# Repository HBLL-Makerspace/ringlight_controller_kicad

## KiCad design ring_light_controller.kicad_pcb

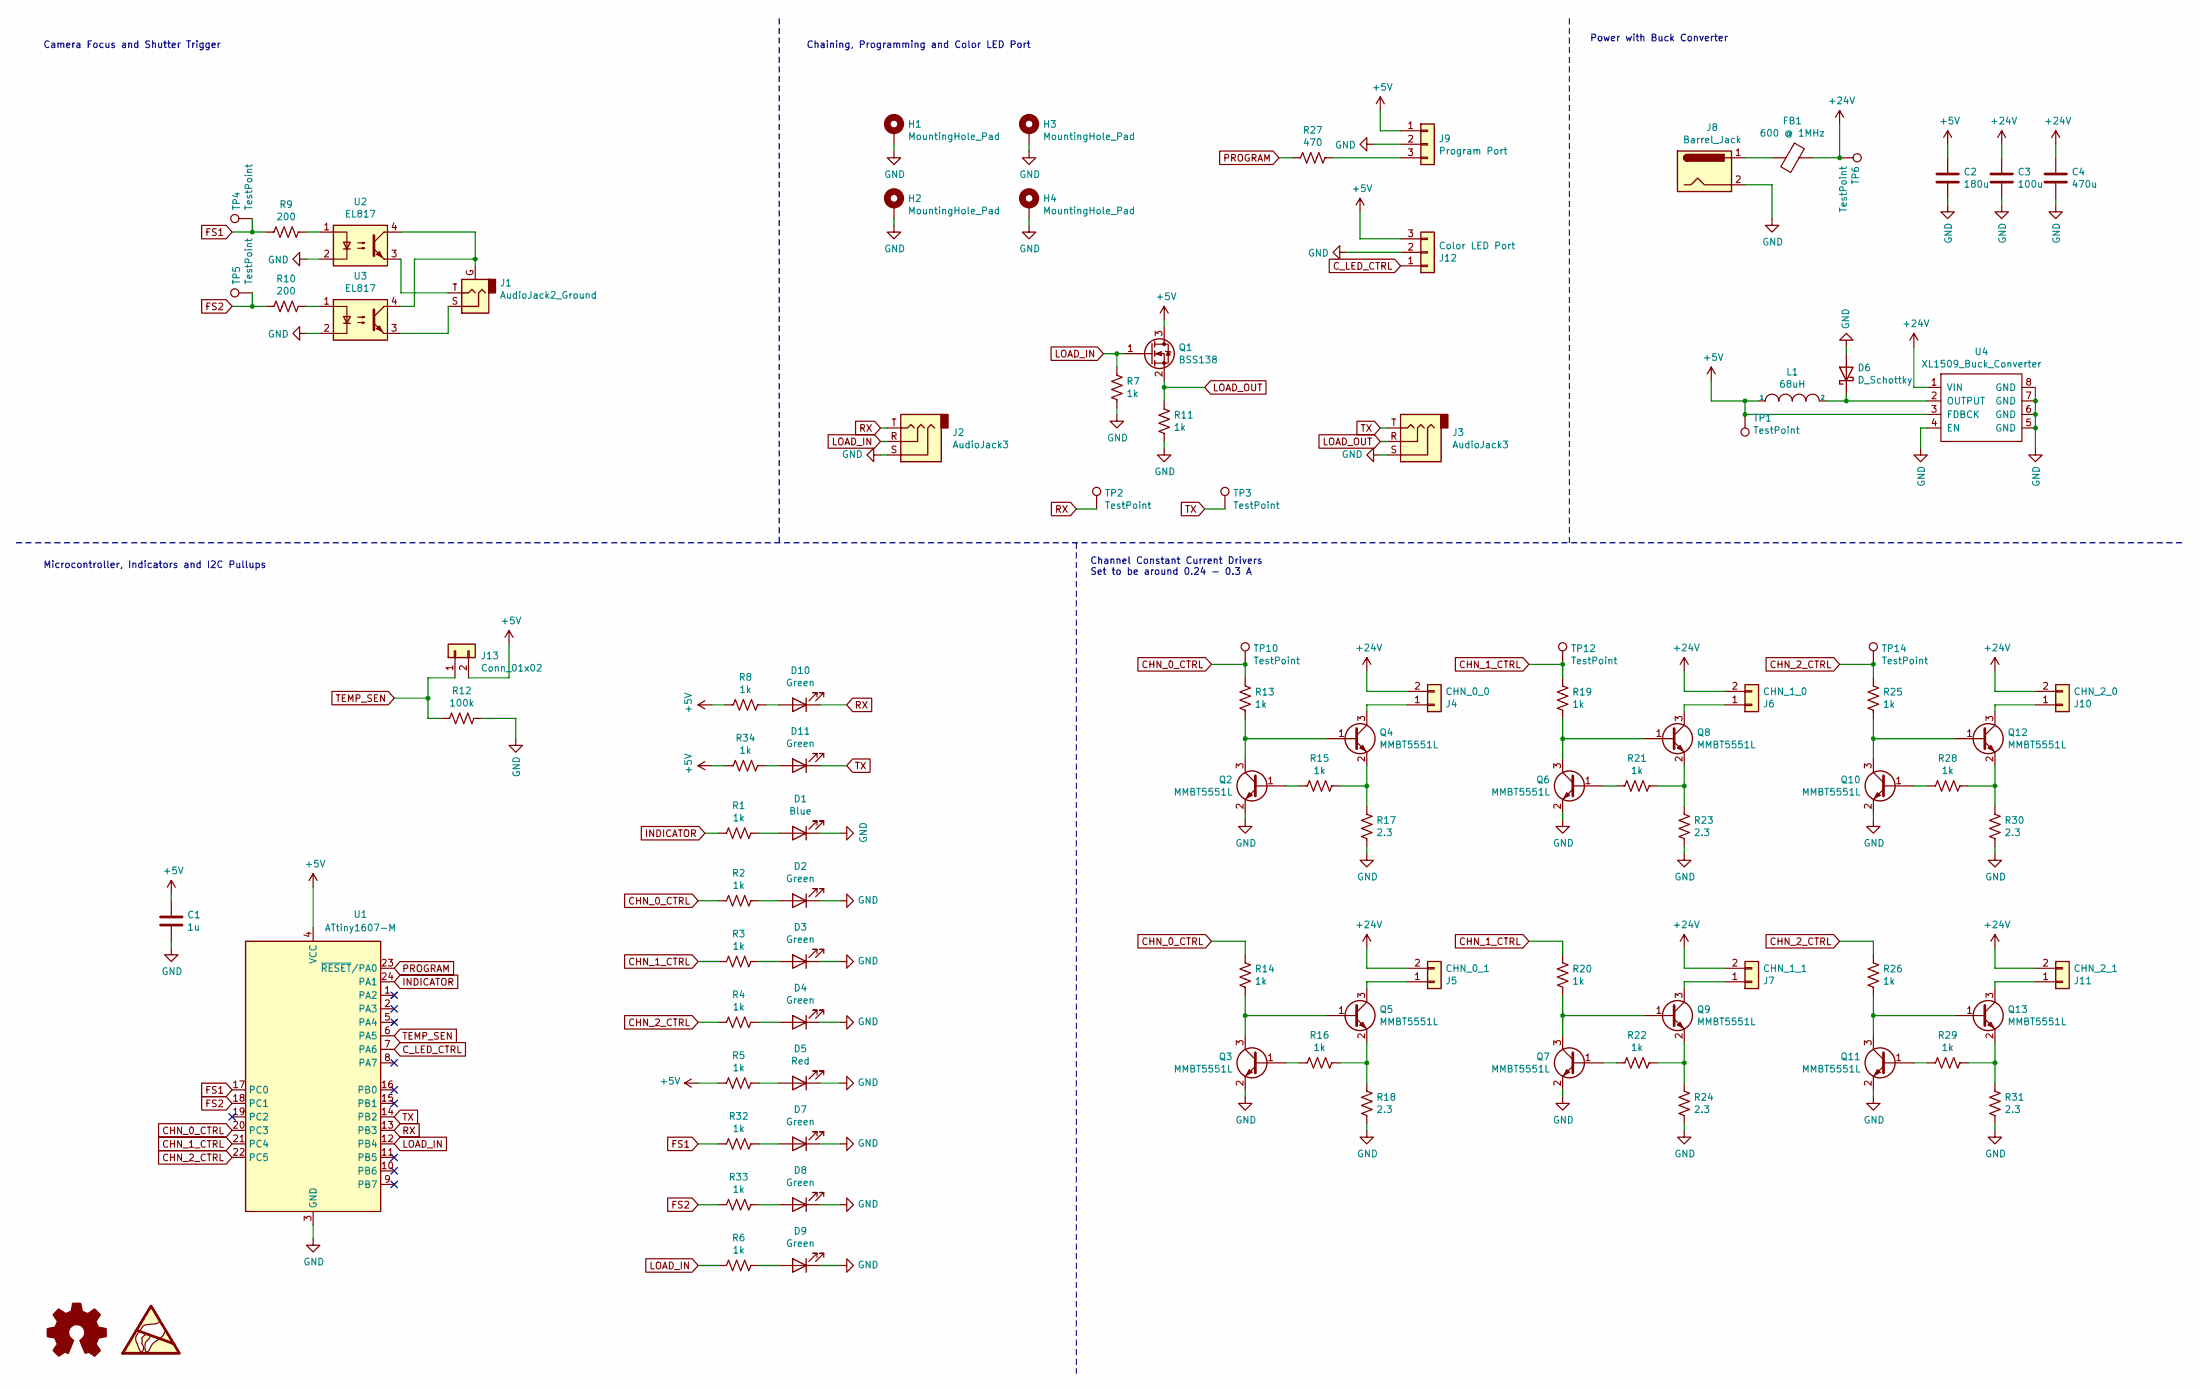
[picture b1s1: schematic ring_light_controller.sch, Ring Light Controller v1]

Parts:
C1: 1u; C_1206_3216Metric; LCSC Part # C1848
C2: 180u; C_Elec_10x10.2; LCSC Part # C487098
C3: 100u; C_Elec_6.3x5.4; LCSC Part # C134723
C4: 470u; C_Elec_10x10.2; LCSC Part # C249931
D1: Blue; LED_0603_1608Metric; LCSC Part # C72041
D2, D3, D4, D7, D8, D9, D10, D11: Green; LED_0603_1608Metric; LCSC Part # C72043
D5: Red; LED_0603_1608Metric; LCSC Part # C2286
D6: D_Schottky; D_SOD-123; LCSC Part # C8598
FB1: 600 @ 1MHz; L_0805_2012Metric; LCSC Part # C1017
H1, H2, H3, H4: MountingHole_Pad; MountingHole_5.3mm_M5_Pad_Via
J1: AudioJack2_Ground; Jack_2.5mm_PJ-2342-SMT; LCSC Part # C397356
J2, J3: AudioJack3; Jack_3.5mm_BOOMELE_C18594-SMT_Horizontal; LCSC C18594
J4: CHN_0_0; JST_XH_B2B-XH-AM_1x02_P2.50mm_Vertical
J5: CHN_0_1; JST_XH_B2B-XH-AM_1x02_P2.50mm_Vertical
J6: CHN_1_0; JST_XH_B2B-XH-AM_1x02_P2.50mm_Vertical
J7: CHN_1_1; JST_XH_B2B-XH-AM_1x02_P2.50mm_Vertical
J8: Barrel_Jack; BarrelJack_Horizontal
J9: Program Port; PinHeader_1x03_P2.54mm_Vertical
J10: CHN_2_0; JST_XH_B2B-XH-AM_1x02_P2.50mm_Vertical
J11: CHN_2_1; JST_XH_B2B-XH-AM_1x02_P2.50mm_Vertical
J12: Color LED Port; JST_XH_B3B-XH-AM_1x03_P2.50mm_Vertical
J13: Conn_01x02; JST_XH_B2B-XH-AM_1x02_P2.50mm_Vertical
L1: 68uH; L_SUNLORD_SWRB1205S_12.5x12.5mm_H6mm; LCSC Part # C169388
Q1: BSS138; SOT-23; LCSC Part # C2145
Q2, Q3, Q4, Q5, Q6, Q7, Q8, Q9, Q10, Q11, Q12, Q13: MMBT5551L; SOT-23; LCSC Part # C2145
R1, R2, R3, R4, R5, R6, R32, R33: 1k; R_0603_1608Metric; LCSC Part # C21190
R7, R11, R13, R14, R15, R16, R19, R20, R21, R22, R25, R26, R28, R29: 1k; R_0402_1005Metric; LCSC Part # C11702
R8, R34: 1k; R_0402_1005Metric; LCSC Part # C21190
R9, R10: 200; R_0402_1005Metric; LCSC Part # C11702
R12: 100k; R_0402_1005Metric; LCSC Part # C25741
R17, R18, R23, R24, R30, R31: 2.3; R_1206_3216Metric; LCSC Part # C247504
R27: 470; R_0402_1005Metric; LCSC Part # C25117
TP1, TP2, TP3, TP4, TP5, TP6, TP10, TP12, TP14: TestPoint; TestPoint_Pad_D1.0mm
U1: ATtiny1607-M; QFN-24-1EP_4x4mm_P0.5mm_EP2.6x2.6mm
U2, U3: EL817; SOIC254P1030X390-4N; LCSC Part # C106900
U4: XL1509_Buck_Converter; SOP-8_3.9x4.9mm_P1.27mm; LCSC Part # C61063

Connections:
+5V: C1.1, C2.1, J9.1, J12.3, J13.2, L1.1, Q1.3 (D), R5.2, R8.2, R34.2, TP1.1, U1.4 (VCC), U4.3 (FDBCK)
+24V: C3.1, C4.1, FB1.1, J4.2, J5.2, J6.2, J7.2, J10.2, J11.2, TP6.1, U4.1 (VIN)
CHN_0_CTRL: R2.2, R13.1, R14.1, TP10.1, U1.20 (PC3); also elsewhere on the board
CHN_1_CTRL: R3.2, R19.1, R20.1, TP12.1, U1.21 (PC4); also elsewhere on the board
CHN_2_CTRL: R4.2, R25.1, R26.1, TP14.1, U1.22 (PC5); also elsewhere on the board
C_LED_CTRL: J12.1, U1.7 (PA6)
FS1: R9.2, R32.2, TP4.1, U1.17 (PC0)
FS2: R10.2, R33.2, TP5.1, U1.18 (PC1)
GND: C1.2, C2.2, C3.2, C4.2, D1.1 (K), D2.1 (K), D3.1 (K), D4.1 (K), D5.1 (K), D6.2 (A), D7.1 (K), D8.1 (K), D9.1 (K), H1.1, H2.1, H3.1, H4.1, J2.S, J3.S, J8.2, J9.2, J12.2, Q2.2 (E), Q3.2 (E), Q6.2 (E), Q7.2 (E), Q10.2 (E), Q11.2 (E), R7.1, R11.1, R12.1, R17.2, R18.2, R23.2, R24.2, R30.2, R31.2, U1.3 (GND), U1.25 (GND), U2.2, U3.2, U4.4 (EN), U4.5 (GND), U4.6 (GND), U4.7 (GND), U4.8 (GND); also elsewhere on the board
INDICATOR: R1.2, U1.24 (PA1)
LOAD_IN: J2.R, Q1.1 (G), R6.2, R7.2, U1.12 (PB4)
LOAD_OUT: J3.R, Q1.2 (S), R11.2
unnamed: D1.2 (A), R1.1
unnamed: D2.2 (A), R2.1
unnamed: D3.2 (A), R3.1
unnamed: D4.2 (A), R4.1
unnamed: D5.2 (A), R5.1
unnamed: D6.1 (K), L1.2, U4.2 (OUTPUT)
unnamed: D7.2 (A), R32.1
unnamed: D8.2 (A), R33.1
unnamed: D9.2 (A), R6.1
unnamed: D10.2 (A), R8.1
unnamed: D11.2 (A), R34.1
unnamed: FB1.2, J8.1
unnamed: J1.G, U2.4, U3.4
unnamed: J1.S, U3.3
unnamed: J1.T, U2.3
unnamed: J4.1, Q4.3 (C)
unnamed: J5.1, Q5.3 (C)
unnamed: J6.1, Q8.3 (C)
unnamed: J7.1, Q9.3 (C)
unnamed: J9.3, R27.1
unnamed: J10.1, Q12.3 (C)
unnamed: J11.1, Q13.3 (C)
unnamed: Q2.1 (B), R15.2
unnamed: Q2.3 (C), Q4.1 (B), R13.2
unnamed: Q3.1 (B), R16.2
unnamed: Q3.3 (C), Q5.1 (B), R14.2
unnamed: Q4.2 (E), R15.1, R17.1
unnamed: Q5.2 (E), R16.1, R18.1
unnamed: Q6.1 (B), R21.2
unnamed: Q6.3 (C), Q8.1 (B), R19.2
unnamed: Q7.1 (B), R22.2
unnamed: Q7.3 (C), Q9.1 (B), R20.2
unnamed: Q8.2 (E), R21.1, R23.1
unnamed: Q9.2 (E), R22.1, R24.1
unnamed: Q10.1 (B), R28.2
unnamed: Q10.3 (C), Q12.1 (B), R25.2
unnamed: Q11.1 (B), R29.2
unnamed: Q11.3 (C), Q13.1 (B), R26.2
unnamed: Q12.2 (E), R28.1, R30.1
unnamed: Q13.2 (E), R29.1, R31.1
unnamed: R9.1, U2.1
unnamed: R10.1, U3.1
PROGRAM: R27.2, U1.23 (~RESET~/PA0)
RX: D10.1 (K), J2.T, TP2.1, U1.13 (PB3)
TEMP_SEN: J13.1, R12.2, U1.6 (PA5)
TX: D11.1 (K), J3.T, TP3.1, U1.14 (PB2)

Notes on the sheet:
Channel Constant Current Drivers Set to be around 0.24 - 0.3 A
Power with Buck Converter
Chaining, Programming and Color LED Port
Microcontroller, Indicators and I2C Pullups
Camera Focus and Shutter Trigger

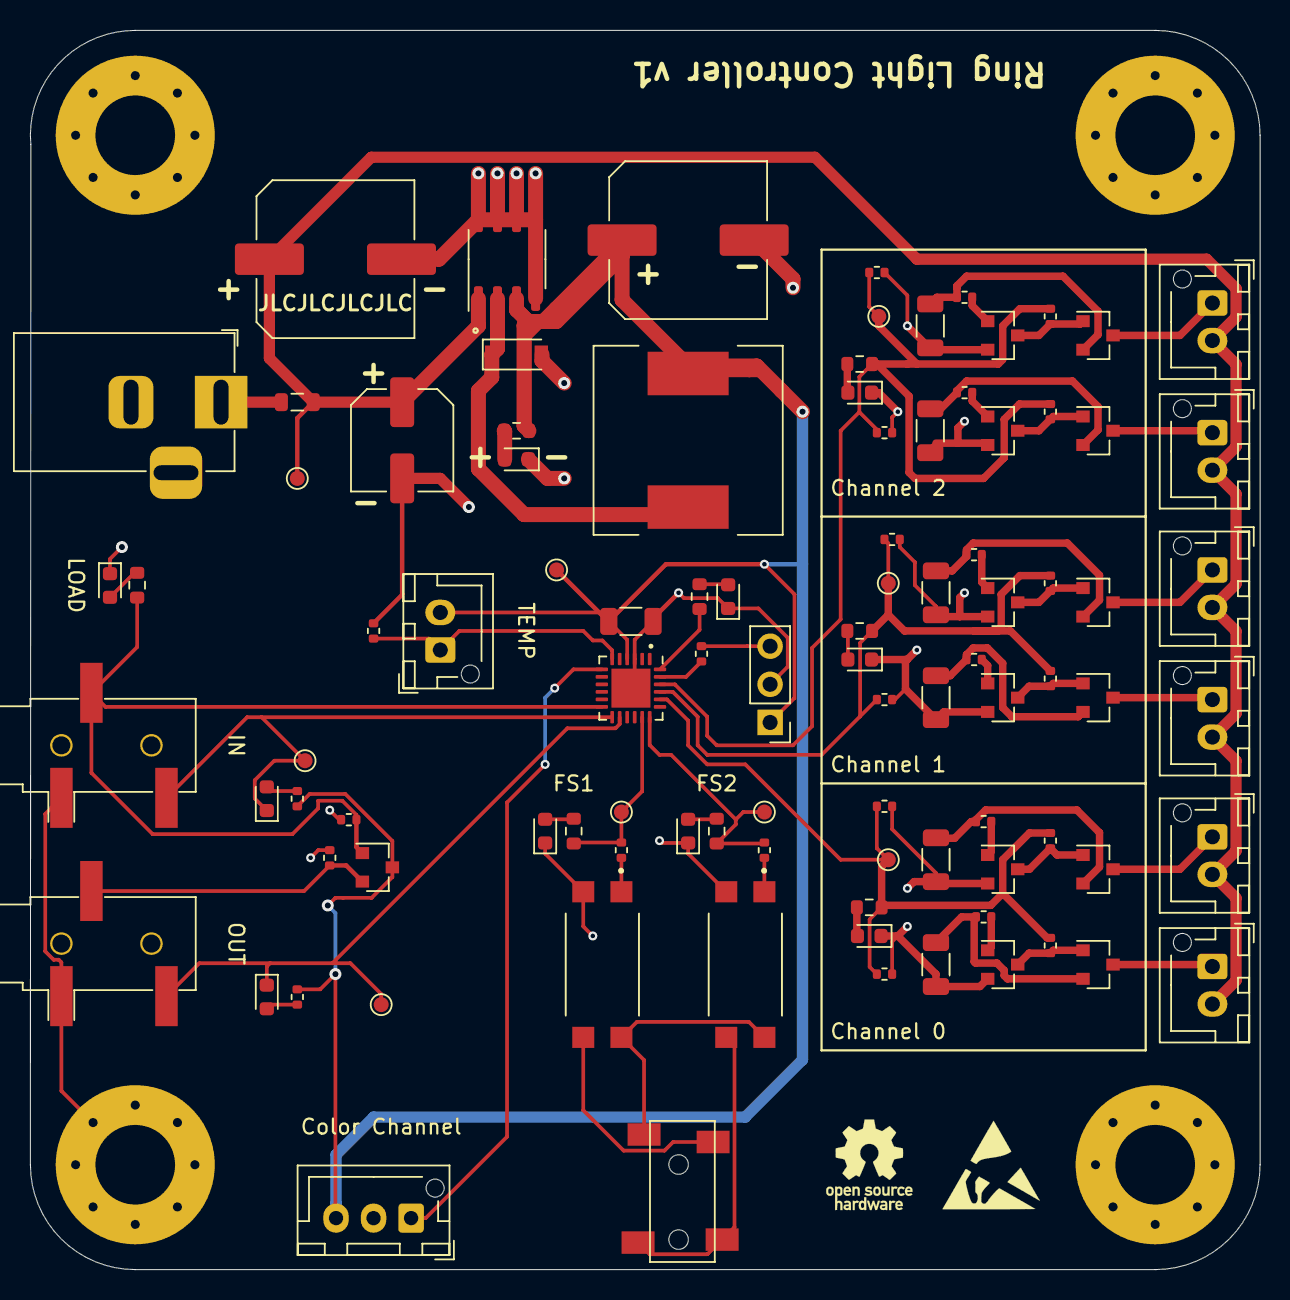
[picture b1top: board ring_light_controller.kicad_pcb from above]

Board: 2 copper layers, 81.9 x 82.6 mm, 100 parts (0 on the bottom side), 58 nets.

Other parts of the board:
R35, R36, R37, R38, R39, R40: 1k; R_0402_1005Metric

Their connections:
CHN_0_CTRL: R35.2, R36.2; also elsewhere on the board
CHN_1_CTRL: R37.2, R38.2; also elsewhere on the board
CHN_2_CTRL: R39.2, R40.2; also elsewhere on the board
GND: R35.1, R36.1, R37.1, R38.1, R39.1, R40.1; also elsewhere on the board

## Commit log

2021-07-09 Updated footprints to work with JLCPCB assembly parts
2021-07-20 updated pcb
2021-07-20 updated version numbering
2021-07-27 updated connecters to 3.5mm, and made opto resistors smaller in value
2021-07-29 slight changes
2021-07-30 fixed opto pin outputs
2022-01-21 updated to latest
